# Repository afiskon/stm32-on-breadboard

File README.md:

# stm32-on-breadboard

Исходники к заметке "Используем STM32 безо всяких отладочных плат".

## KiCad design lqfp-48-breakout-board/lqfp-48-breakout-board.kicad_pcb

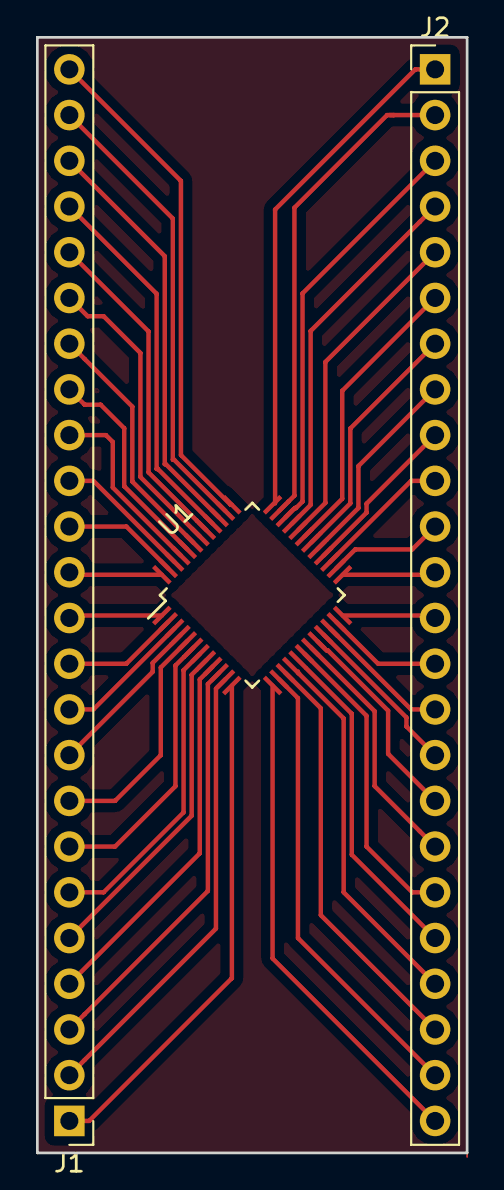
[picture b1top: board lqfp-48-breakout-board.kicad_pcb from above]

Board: 2 copper layers, 23.9 x 62.0 mm, 3 parts (0 on the bottom side), 48 nets.

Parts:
J1, J2: Conn_01x24; Pin_Header_Straight_1x24_Pitch2.54mm
U1: STM32F103C8Tx; LQFP-48_7x7mm_Pitch0.5mm

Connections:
J1_01: J1.1, U1.12
J1_02: J1.2, U1.11
J1_03: J1.3, U1.10
J1_04: J1.4, U1.9
J1_05: J1.5, U1.8
J1_06: J1.6, U1.7
J1_07: J1.7, U1.6
J1_08: J1.8, U1.5
J1_09: J1.9, U1.4
J1_10: J1.10, U1.3
J1_11: J1.11, U1.2
J1_12: J1.12, U1.1
J1_13: J1.13, U1.48
J1_14: J1.14, U1.47
J1_15: J1.15, U1.46
J1_16: J1.16, U1.45
J1_17: J1.17, U1.44
J1_18: J1.18, U1.43
J1_19: J1.19, U1.42
J1_20: J1.20, U1.41
J1_21: J1.21, U1.40
J1_22: J1.22, U1.39
J1_23: J1.23, U1.38
J1_24: J1.24, U1.37
J2_01: J2.1, U1.36
J2_02: J2.2, U1.35
J2_03: J2.3, U1.34
J2_04: J2.4, U1.33
J2_05: J2.5, U1.32
J2_06: J2.6, U1.31
J2_07: J2.7, U1.30
J2_08: J2.8, U1.29
J2_09: J2.9, U1.28
J2_10: J2.10, U1.27
J2_11: J2.11, U1.26
J2_12: J2.12, U1.25
J2_13: J2.13, U1.24
J2_14: J2.14, U1.23
J2_15: J2.15, U1.22
J2_16: J2.16, U1.21
J2_17: J2.17, U1.20
J2_18: J2.18, U1.19
J2_19: J2.19, U1.18
J2_20: J2.20, U1.17
J2_21: J2.21, U1.16
J2_22: J2.22, U1.15
J2_23: J2.23, U1.14
J2_24: J2.24, U1.13

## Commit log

2018-01-21 LQFP-48 breakout board KiCad and gerber files added
2018-01-21 Firmware template created in STM32CubeMX
2018-01-21 Makefile updated
2018-01-21 main.c updated
2018-01-21 Minor changes
2018-01-30 Enable SWD
